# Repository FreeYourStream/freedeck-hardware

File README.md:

# FreeDeck

## Be careful when printing cases. PCB rev 1.1 - 1.3 has new dimensions. Most cases on thingiverse are still for rev 1.0!

The first cases for Rev 1.1 / 1.2 / 1.3 can be found in the wiki (See link below)

## This Repo contains all the stuff you need to build your own FreeDeck

- [Walkthrough and tutorial](https://youtu.be/-3Zw8hbpVq4) video from Adam Welch
- [Demo Video](https://www.youtube.com/watch?v=_TcliiU2K48) of my first prototype

### [Discord Community](https://discord.gg/sEt2Rrd)

## Description

The FreeDeck aims to be a Free/OpenSource replacement for Elgatos Streamdeck and similar.
It works by creating a config file with the FreeDeck [Configurator](https://fdconfig.freeyourstream.com/), loading it onto an SDCard and inserting it into the FreeDeck. You don't need to install any software and can use it across reboots on Windows, Linux and MacOS. This was my main reason behind this gadget.
This prototype is made from:

- Perfboard
- Arduino Pro Micro (32u4 16mhz 5v)
- 2x 4051 Multiplexer
- 6x ssd1306 OLEDs
- 6x 3x4x2mm SMD buttons
- SPI-SDcard Reader

The Arduino Code can be found [here](https://github.com/koriwi/freedeck-ino)

The Configurator Repo can be found [here](https://github.com/koriwi/freedeck-configurator)

A wiki on how to construct it can be found [here](https://github.com/FreeYourStream/freedeck-wiki/wiki)

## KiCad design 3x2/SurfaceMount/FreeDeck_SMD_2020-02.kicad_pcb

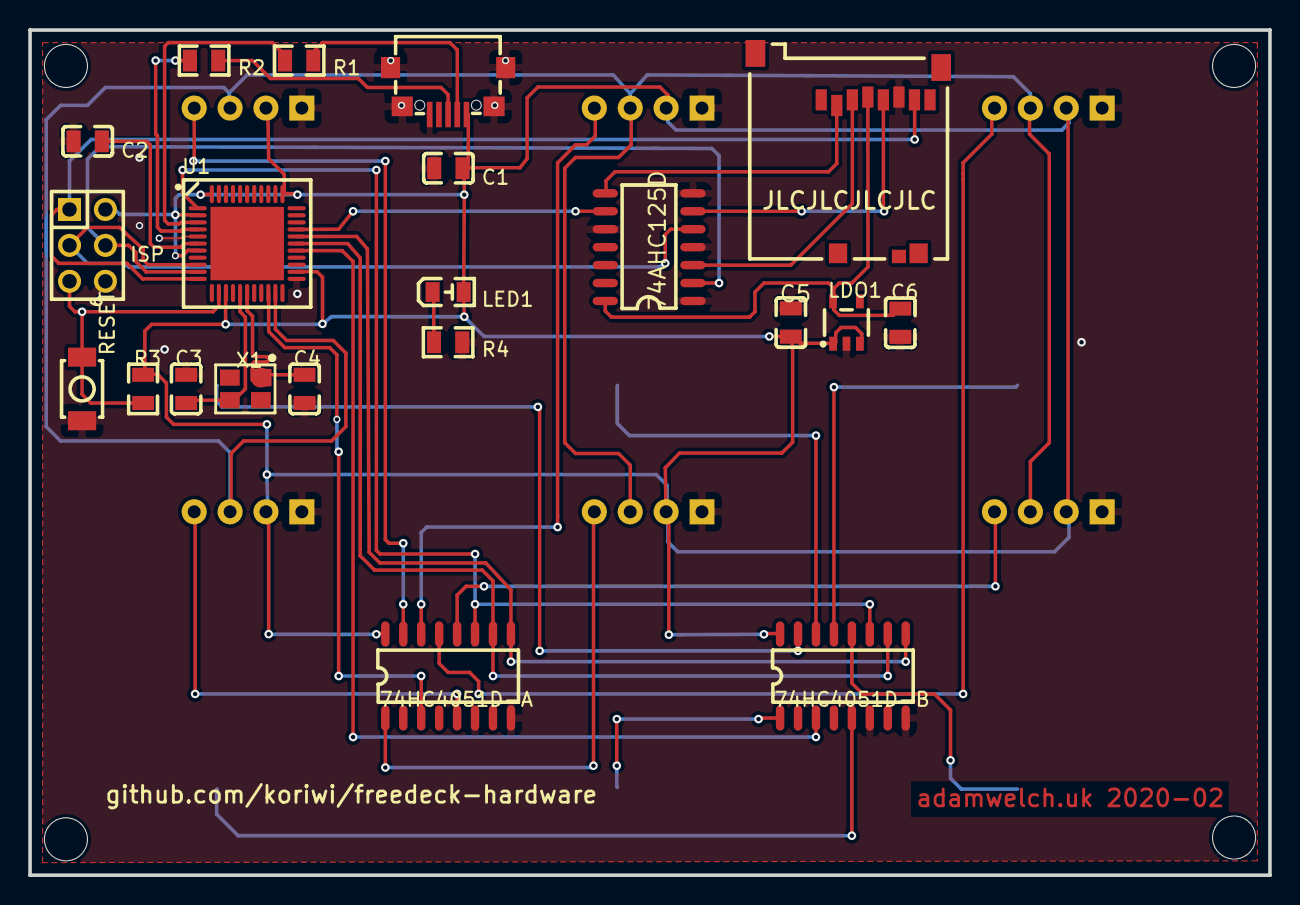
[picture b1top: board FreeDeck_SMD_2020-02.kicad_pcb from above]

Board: 2 copper layers, 87.8 x 59.8 mm, 33 parts (0 on the bottom side), 37 nets.

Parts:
74AHC125D: 74AHC125D; SOIC-14_L8.7-W3.9-P1.27-LS6.0-BL
74HC4051D-A, 74HC4051D-B: 74HC4051D,653; SOIC-16_L9.9-W3.9-P1.27-LS6.0-BL
C1: 100n; C0805
C2, C5, C6: 1u; C0805
C3, C4: 22p; C0805
CARD1: 473521001; SD-SMD_SD-47352-101
ISP: 6; HEADER_PRG_2X03
LDO1: ME6211C33M5G-N; SOT-23-5_L3.0-W1.7-P0.95-LS2.8-BL
LED1: BLUE; LED0805-RD
OLED1, OLED2, OLED3, OLED4, OLED5, OLED6: SDA; SSD1306_ARDUINO
R1, R2: 22R; R0805
R3: 10k; R0805
R4: 470R; R0805
RESET: TS-1088R-02026; SW-SMD_L3.9-W3.0-P4.45
SW1, SW2, SW3, SW4, SW5, SW6: TS-1088R-02026; SW-SMD_L3.9-W3.0-P4.45
U1: ATMEGA32U4-MU; VQFN-44_L7.0-W7.0-P0.50-BL-EP5.2
USB1: micro 5P_C77238; MICRO-USB_MICRO-USB-17
X1: 16MHz; OSC-SMD_4P-L3.2-W2.5-BL

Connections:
+5V: 74HC4051D-A.16, 74HC4051D-B.16, C1.1, C5.2, ISP.2, LDO1.1, LDO1.3, LED1.2, OLED1.2, OLED2.2, OLED3.2, OLED4.2, OLED5.2, OLED6.2, R3.1, U1.2, U1.7, U1.14, U1.24, U1.34, U1.44, USB1.1
A: 74HC4051D-A.11, 74HC4051D-B.11, U1.1
B: 74HC4051D-A.10, 74HC4051D-B.10, U1.28
C: 74HC4051D-A.9, 74HC4051D-B.9, U1.29
CLK: 74AHC125D.5, ISP.3, U1.9
CLK2: 74AHC125D.6, CARD1.5
CS: 74AHC125D.9, U1.30
CS2: 74AHC125D.8, CARD1.2
D+: R2.1, USB1.3
D-: R1.1, USB1.2
GND: 74AHC125D.1, 74AHC125D.4, 74AHC125D.7, 74AHC125D.10, 74HC4051D-A.6, 74HC4051D-A.8, 74HC4051D-B.6, 74HC4051D-B.8, C1.2, C2.2, C3.2, C4.2, C5.1, C6.1, CARD1.6, ISP.6, LDO1.2, OLED1.1, OLED2.1, OLED3.1, OLED4.1, OLED5.1, OLED6.1, R4.2, RESET.2, SW1.1, SW2.1, SW3.1, SW4.1, SW5.1, SW6.1, U1.5, U1.15, U1.23, U1.35, U1.43, USB1.0, USB1.5
MISO: CARD1.7, ISP.1, U1.11
MOSI: 74AHC125D.2, ISP.4, U1.10
MOSI2: 74AHC125D.3, CARD1.3
R4_1: LED1.1, R4.1
RESET: ISP.5, R3.2, RESET.1, U1.13
SCK: OLED1.3, OLED2.3, OLED3.3, OLED4.3, OLED5.3, OLED6.3, U1.21
SDA1: 74HC4051D-A.13, OLED1.4
SDA2: 74HC4051D-A.14, OLED2.4
SDA3: 74HC4051D-A.15, OLED3.4
SDA4: 74HC4051D-A.12, OLED4.4
SDA5: 74HC4051D-A.1, OLED5.4
SDA6: 74HC4051D-A.5, OLED6.4
SW1: 74HC4051D-B.13, SW1.2
SW2: 74HC4051D-B.14, SW2.2
SW3: 74HC4051D-B.15, SW3.2
SW4: 74HC4051D-B.12, SW4.2
SW5: 74HC4051D-B.1, SW5.2
SW6: 74HC4051D-B.5, SW6.2
U1_3: R1.2, U1.3
U1_4: R2.2, U1.4
U1_6: C2.1, U1.6
U1_16: C3.1, U1.16, X1.3
U1_17: C4.1, U1.17, X1.1
VCC: 74AHC125D.14, C6.2, CARD1.4, LDO1.5
X1: 74HC4051D-A.3, U1.20
X2: 74HC4051D-B.3, U1.27

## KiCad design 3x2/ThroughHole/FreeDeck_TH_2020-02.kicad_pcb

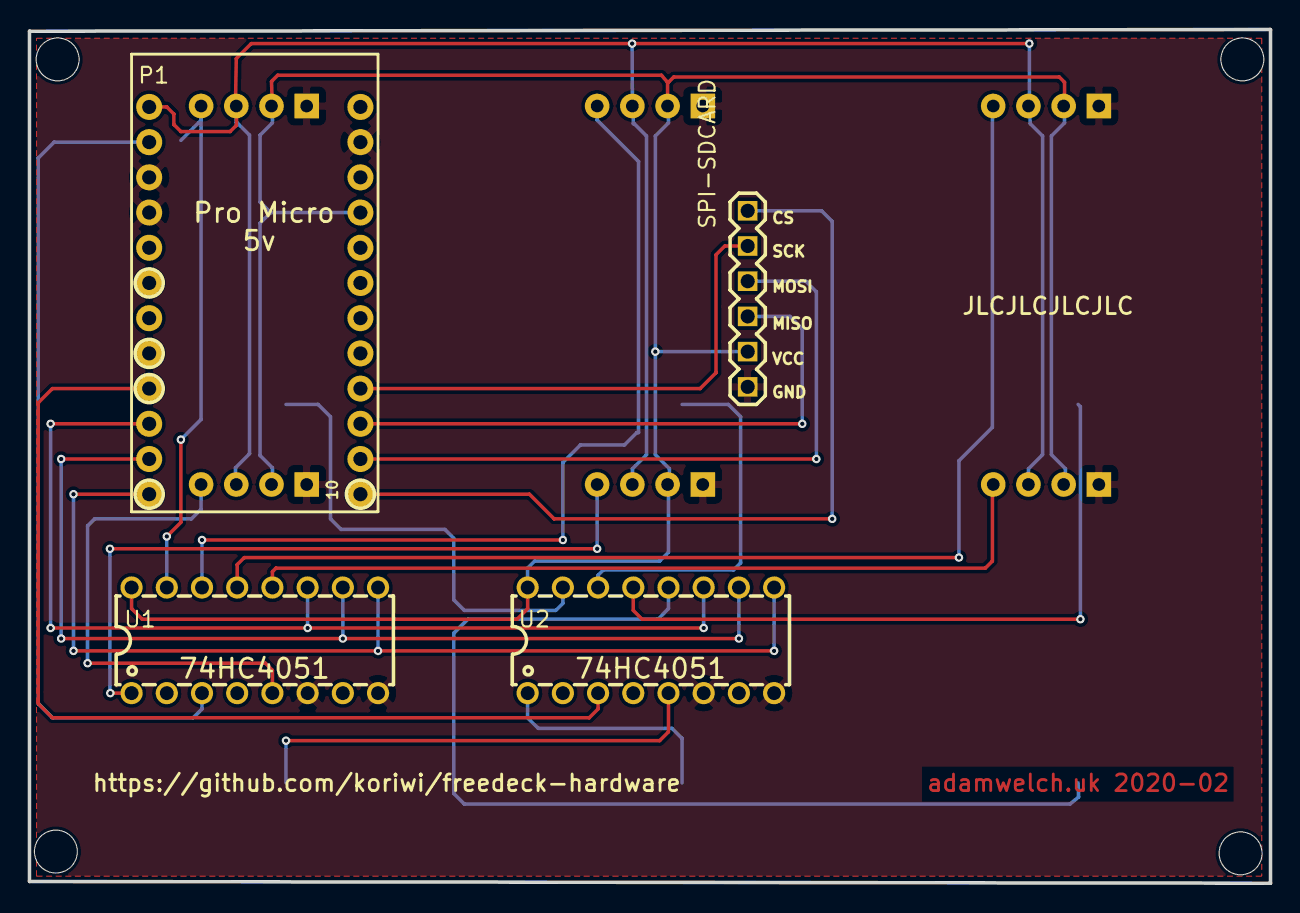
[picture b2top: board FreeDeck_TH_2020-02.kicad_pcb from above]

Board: 2 copper layers, 89.5 x 61.6 mm, 16 parts (0 on the bottom side), 24 nets.

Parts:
OLED1, OLED2, OLED3, OLED4, OLED5, OLED6: SDA; SSD1306_ARDUINO
P1: 10; PRO MICRO - 5V
SPI-SDCARD: HEADER-06X1-MALE; 06X1-PTH
SW1, SW2, SW3, SW4, SW5, SW6: TS-1088R-02026; SW-SMD_L3.9-W3.0-P4.45
U1, U2: CD74HC4051E; DIP-16_L20.0-W6.4-P2.54-LS7.6-BL

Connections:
+5V: OLED1.2, OLED2.2, OLED3.2, OLED4.2, OLED5.2, OLED6.2, P1.16, SPI-SDCARD.2, U1.16, U2.16
A: P1.3, U1.11, U2.11
B: P1.2, U1.10, U2.10
C: P1.1, U1.9, U2.9
CS: P1.24, SPI-SDCARD.6
GND: OLED1.1, OLED2.1, OLED3.1, OLED4.1, OLED5.1, OLED6.1, P1.9, P1.10, P1.14, SPI-SDCARD.1, SW1.2, SW2.2, SW3.2, SW4.2, SW5.2, SW6.2, U1.6, U1.8, U2.6, U2.8
MISO: P1.22, SPI-SDCARD.3
MOSI: P1.23, SPI-SDCARD.4
SCK: P1.21, SPI-SDCARD.5
SCL: OLED1.3, OLED2.3, OLED3.3, OLED4.3, OLED5.3, OLED6.3, P1.12
SDA1: OLED1.4, U1.13
SDA2: OLED2.4, U1.14
SDA3: OLED3.4, U1.15
SDA4: OLED4.4, U1.12
SDA5: OLED5.4, U1.1
SDA6: OLED6.4, U1.5
SW1: SW1.1, U2.13
SW2: SW2.1, U2.14
SW3: SW3.1, U2.15
SW4: SW4.1, U2.12
SW5: SW5.1, U2.1
SW6: SW6.1, U2.5
X1: P1.11, U1.3
X2: P1.4, U2.3

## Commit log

2020-04-10 first horrible version
    cant upload pcb file right now. fritzing keeps crashing. help appreciated
2020-04-11 3d-drawings
2020-04-11 move displays
    moves display by 0.6mm
2020-04-11 added first case prototype
2020-06-17 New PCB designs
2020-07-02 remove legacy files
2020-07-02 include adams video
2020-07-02 reformat readme
2020-07-17 KiCAD PCB File
2020-07-21 EasyEDA Source Files
2020-08-23 update image in readme
2020-11-29 adds rev 1.1 pcb files
2020-12-28 Update LICENSE
2021-03-03 reorganize old and new pcbs
2021-04-18 [Case] Added case for PCB v1.1 & v1.2
2021-04-18 [README] Some changes in the readme
2021-10-13 Added file for 1.3
2021-10-13 Added changelog
2022-03-23 Added PCB Rev1.3 (#27)
    * Added file for 1.3
    * Updated README.md
    * Added changelog
2022-05-30 reorganize and add pi pico+case
2022-05-30 reorganize and add pi pico+case (#29)
